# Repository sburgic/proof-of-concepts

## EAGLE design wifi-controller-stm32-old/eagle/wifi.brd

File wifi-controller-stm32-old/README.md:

In order to build project following steps are required:

1. Run cmake configuration script
    1. configure-windows.bat - Windows host, debug version
    2. configure-windows-release.bat - Windows host, release version
    3. configure-linux.sh - Linux host, debug version
    4. configure-linux-release.sh - Linux host, release version
    
2. Go to build-stm32f1-gcc folder ( if it has not already been automatically done from configure script )
   and type make wifi.bin ( or make wifi.bin size - to obtain image size )
   
In order to flash image run load_image_to_flash.sh script from build-stm32f1-gcc folder ( This script can be executed only on Linux )
To flash image using Windows host use STM32 ST-LINK Utility

Tools:
    gcc-arm-none-eabi compiler
    texane st-util for linux
    cmake

Manuals and datasheets in docs folder

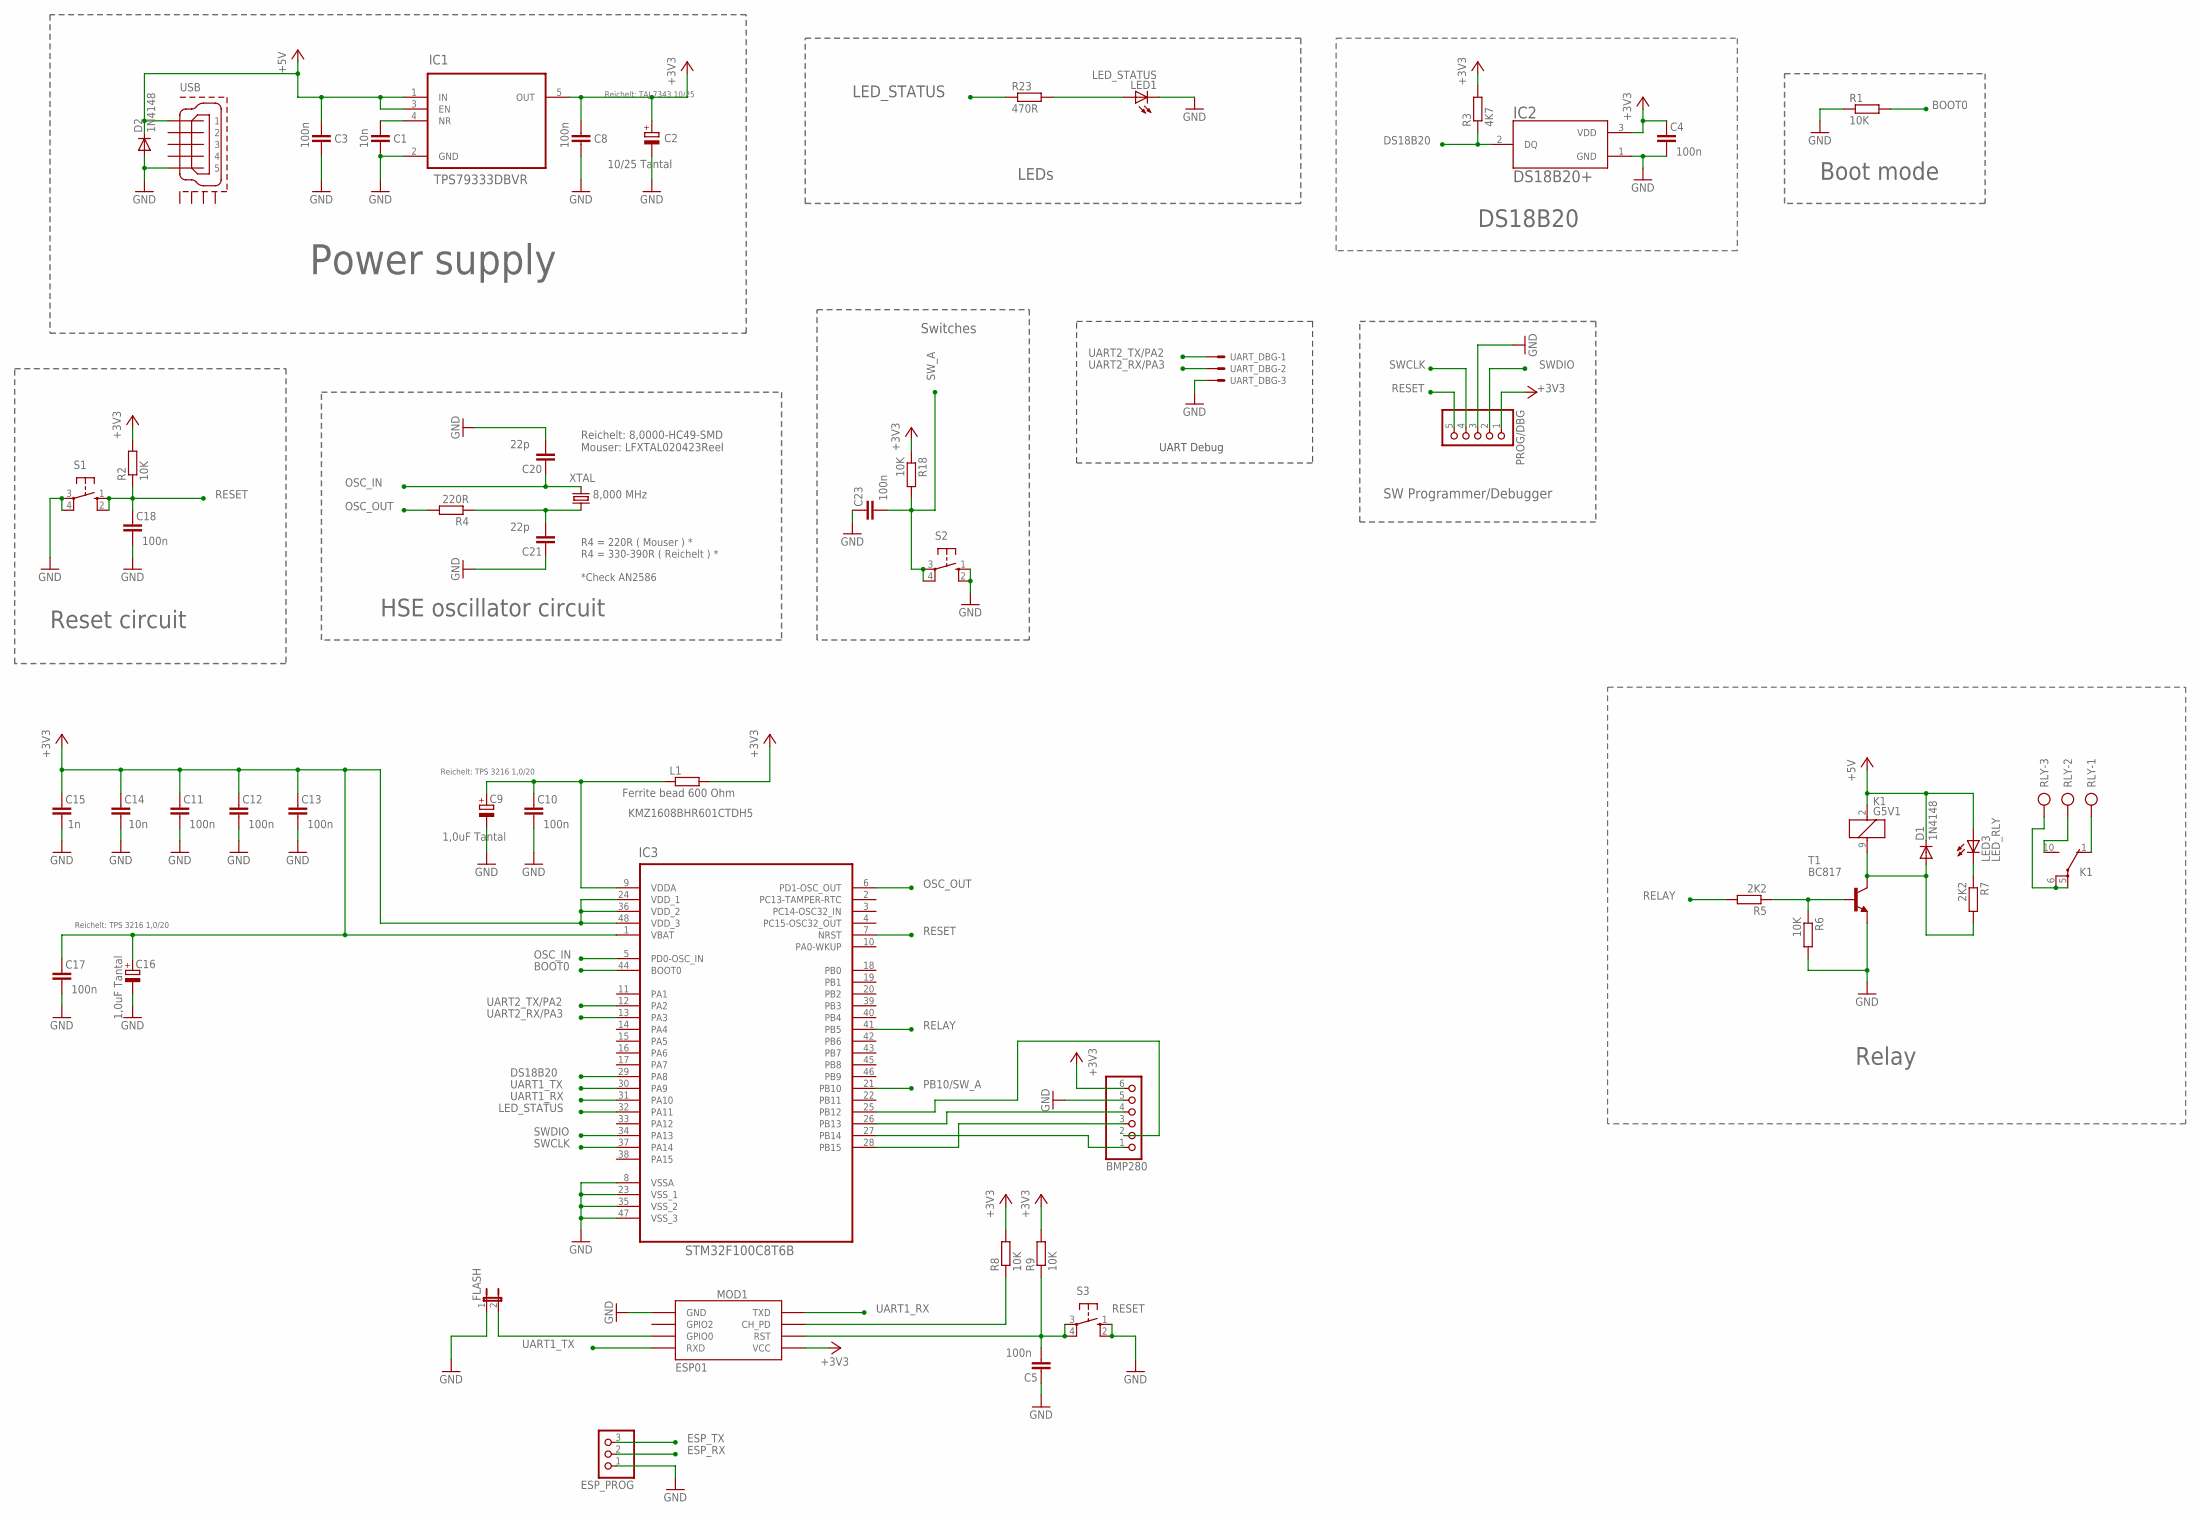
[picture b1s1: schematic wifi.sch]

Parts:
BMP280: PINHD-1X6; 1X06
C1: 10n; C0805
C2: 10/25 Tantal; SMC_D
C3, C4, C5, C8, C23: 100n; C0805
C9, C16: 1,0uF Tantal; SMC_A
C10, C11, C12, C13, C17: 100n; C0402K
C14: 10n; C0402K
C15: 1n; C0402K
C18: 100n; C0603K
C20, C21: 22p; C0603K
D1, D2: 1N4148; DO35-7
ESP_PROG: PINHD-1X3; 1X03
FLASH: JP1E; JP1
IC1: TPS79333DBVR; SOT95P280X145-5N
IC2: DS18B20+; TO-92
IC3: STM32F100C8T6B; QFP50P900X900X160-48N
K1: G5V1
L1: Ferrite bead 600 Ohm; R0603
LED1: LED_STATUS; LED3MM
LED3: LED_RLY; LED3MM
MOD1: ESP01
PROG/DBG: PINHD-1X5; 1X05
R1: 10K; R0805
R2, R6, R8, R9: 10K; R0603
R3: 4K7; R0603
R4: 220R; R0603
R5: 2K2; R0603
R7: 2K2; R0805
R18: 10K; M0805
R23: 470R; R0805
RLY: AK300/3
S1, S2, S3: 10-XX; B3F-10XX
T1: BC817; SOT23-BEC
UART_DBG: 22-23-2031
USB: MICRO-USB-RECEPTACLE47589-0001; 47589-0001
XTAL: 8,000 MHz; SM49

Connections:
+3V3: BMP280.6, C2.+, C4.1, C8.1, C11.1, C12.1, C13.1, C14.1, C15.1, C16.+, C17.1, IC1.5 (OUT), IC2.3 (VDD), IC3.1 (VBAT), IC3.24 (VDD_1), IC3.36 (VDD_2), IC3.48 (VDD_3), L1.2, MOD1.VCC, PROG/DBG.1, R2.2, R3.2, R8.2, R9.2, R18.1
+5V: C3.1, D1.C, D2.C, IC1.1 (IN), IC1.3 (EN), K1.2 (1), LED3.A, USB.1
BOOT0: IC3.44 (BOOT0), R1.2
DS18B20: IC2.2 (DQ), IC3.29 (PA8), R3.1
GND: BMP280.5, C1.2, C2.-, C3.2, C4.2, C5.1, C8.2, C9.-, C10.2, C11.2, C12.2, C13.2, C14.2, C15.2, C16.-, C17.2, C18.2, C20.2, C21.1, C23.1, D2.A, ESP_PROG.1, FLASH.1, IC1.2 (GND), IC2.1 (GND), IC3.8 (VSSA), IC3.23 (VSS_1), IC3.35 (VSS_2), IC3.47 (VSS_3), LED1.K (C), MOD1.GND, PROG/DBG.3, R1.1, R6.2, S1.3, S1.4 (P1), S2.1 (S), S2.2 (S1), S3.1 (S), S3.2 (S1), T1.E, UART_DBG.3, USB.5
LED_STATUS: IC3.32 (PA11), R23.1
unnamed: C1.1, IC1.4 (NR)
unnamed: K1.1 (O), RLY.1
unnamed: C9.+, C10.1, IC3.9 (VDDA), L1.1
unnamed: K1.10 (S), RLY.2
unnamed: K1.5, K1.6, RLY.3
unnamed: C21.2, R4.1, XTAL.2
unnamed: D1.A, K1.9 (2), R7.2, T1.C
unnamed: R5.1, R6.1, T1.B
unnamed: LED3.K (C), R7.1
unnamed: FLASH.2, MOD1.GPIO0
unnamed: MOD1.CH_PD, R8.1
unnamed: C5.2, MOD1.RST, R9.1, S3.3, S3.4 (P1)
unnamed: BMP280.4, IC3.26 (PB13)
unnamed: BMP280.3, IC3.28 (PB15)
unnamed: BMP280.2, IC3.25 (PB12)
unnamed: BMP280.1, IC3.27 (PB14)
unnamed: LED1.A, R23.2
OSC_IN: C20.1, IC3.5 (PD0-OSC_IN), XTAL.1
OSC_OUT: IC3.6 (PD1-OSC_OUT), R4.2
PB10: C23.2, IC3.21 (PB10), R18.2, S2.3, S2.4 (P1)
RELAY: IC3.41 (PB5), R5.2
RESET: C18.1, IC3.7 (NRST), PROG/DBG.5, R2.1, S1.1 (S), S1.2 (S1)
SWCLK: IC3.37 (PA14), PROG/DBG.4
SWDIO: IC3.34 (PA13), PROG/DBG.2
UART1_RX: ESP_PROG.3, IC3.31 (PA10), MOD1.TX (TXD)
UART1_TX: ESP_PROG.2, IC3.30 (PA9), MOD1.RX (RXD)
UART2_RX: IC3.13 (PA3), UART_DBG.2
UART2_TX: IC3.12 (PA2), UART_DBG.1

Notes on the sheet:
KMZ1608BHR601CTDH5
RESET
OSC_OUT
OSC_IN
Reichelt: 8,0000-HC49-SMD Mouser: LFXTAL020423Reel
R4 = 220R ( Mouser ) * R4 = 330-390R ( Reichelt ) * *Check AN2586
BOOT0
UART1_TX
UART1_RX
DS18B20
SWDIO
SWCLK
SW_A
Switches
Power supply
Reset circuit
HSE oscillator circuit
Boot mode
LED_STATUS
LEDs
PB10/SW_A
UART2_TX/PA2
UART2_RX/PA3
Reichelt: TPS 3216 1,0/20
Reichelt: TAJ 7343 10/25
UART Debug
SW Programmer/Debugger
RELAY
Relay
ESP_TX
ESP_RX

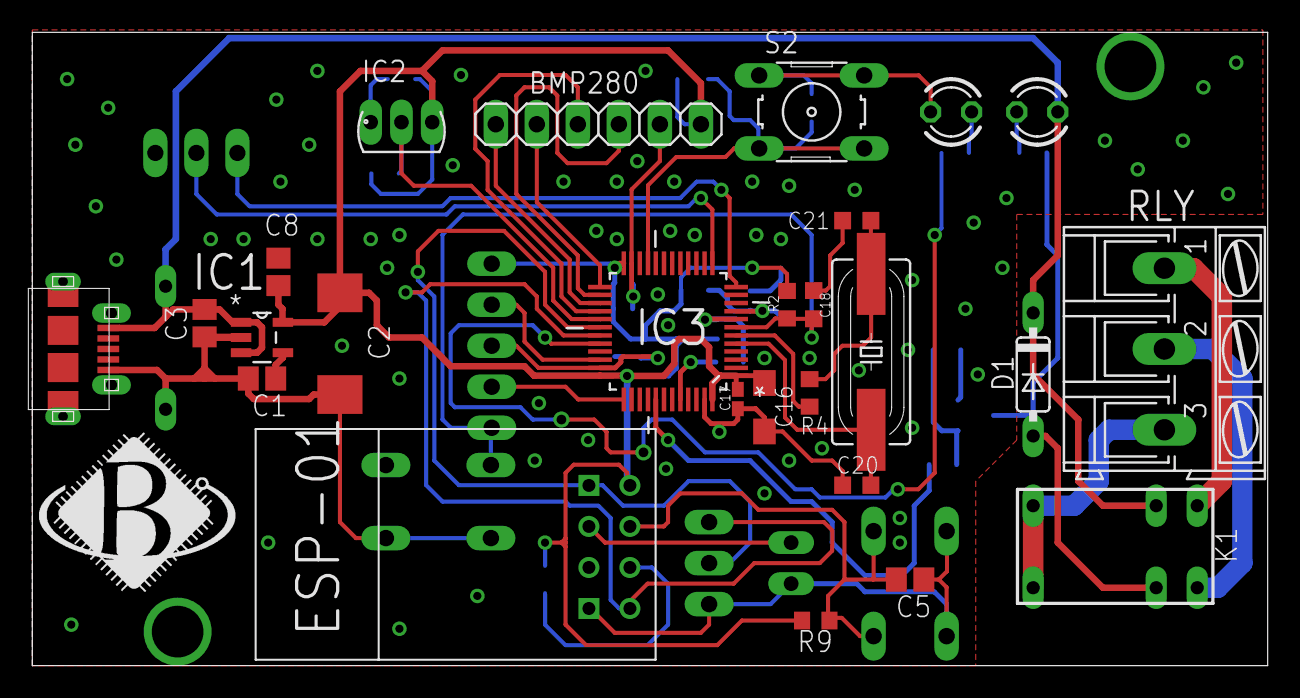
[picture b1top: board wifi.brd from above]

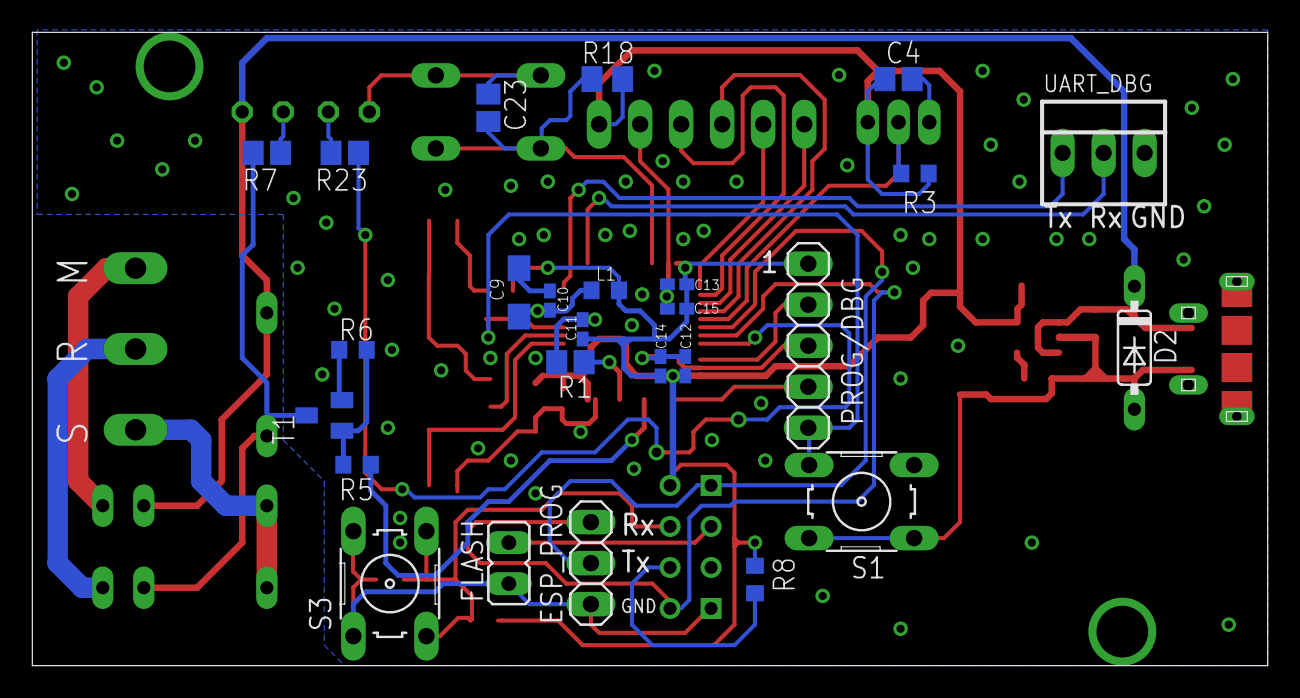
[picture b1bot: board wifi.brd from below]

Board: 2 copper layers, 76.5 x 39.2 mm, 52 parts (26 on the bottom side), 34 nets.

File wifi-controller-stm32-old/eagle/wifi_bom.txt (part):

Partlist exported from D:/!electronics/!projects/wifi/!eagle/wifi.sch at 05/03/2018 22:39:37

Qty Value                Device         Package               Parts                   Description                                                   AVAILABILITY CENTERLINE_(PITCH) COMMENT   DESCRIPTION                                                                                                      MF                   MP             MPN        NUMBER_OF_POSITIONS OC_FARNELL       OC_NEWARK PACKAGE                     PRICE    PRODUCT_TYPE SPICEPREFIX
2                        10-XX          B3F-10XX              S1, S2                  OMRON SWITCH                                                                                                                                                                                                                                                 B3F-1000                       176432           36M3542                                                                
1                        1932788-1      TE_1932788-1          USB                     UUSB 2-DIP REVERSE MOUNT                                      Good         .65 mm[.025 in]    1932788-1  Conn Micro USB RCP 5 POS 0.65mm Solder RA SMD 5 Terminal 1 Port T/R                                             TE                   1932788-1                 5                                              DIP-2 TE Connectivity / AMP 1.46 USD Connector               
1                        22-23-2031     22-23-2031            UART_DBG                .100" (2.54mm) Center Header - 3 Pin                                                                                                                                                                                     MOLEX                               22-23-2031                     1462950          30C0862                                                                
1                        AK300/3        AK300/3               RLY                     CONNECTOR                                                                                                                                                                                                                                                                                   unknown          unknown                                                                
1                        PINHD-1X5      1X05                  PROG/DBG                PIN HEADER                                                                                                                                                                                                                                                                                                                                                                          
2   1,0uF Tantal         CPOL-EUSMCA    SMC_A                 C9, C16                 POLARIZED CAPACITOR, European symbol                                                                                                                                                                                                                                                                                                                                                
1   10/25 Tantal         CPOL-EUSMCD    SMC_D                 C2                      POLARIZED CAPACITOR, European symbol                                                                                                                                                                                                                                                                                                                                                
5   100n                 C-EUC0402K     C0402K                C10, C11, C12, C13, C17 CAPACITOR, European symbol                                                                                                                                                                                                                                                                                                                                               C          
1   100n                 C-EUC0603K     C0603K                C18                     CAPACITOR, European symbol                                                                                                                                                                                                                                                                                                                                               C          
4   100n                 C-EUC0805      C0805                 C3, C4, C8, C23         CAPACITOR, European symbol                                                                                                                                                                                                                                                                                                                                               C          
1   10K                  R-EU_M0805     M0805                 R18                     RESISTOR, European symbol                                                                                                                                                                                                                                                                                                                                                R          
2   10K                  R-EU_R0603     R0603                 R2, R6                  RESISTOR, European symbol                                                                                                                                                                                                                                                                                                                                                R          
1   10K                  R-EU_R0805     R0805                 R1                      RESISTOR, European symbol                                                                                                                                                                                                                                                                                                                                                R          
1   10n                  C-EUC0402K     C0402K                C14                     CAPACITOR, European symbol                                                                                                                                                                                                                                                                                                                                               C          
1   10n                  C-EUC0805      C0805                 C1                      CAPACITOR, European symbol                                                                                                                                                                                                                                                                                                                                               C          
2   1N4148               1N4148DO35-7   DO35-7                D1, D2                  DIODE                                                                                                                                                                                                                                                                                                                                                                               
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
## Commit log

2023-03-21 Add initial projects

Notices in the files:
parts and their libraries:
con-molex-usb: (C) 2014 Tomasz Boleslaw CEDRO, cederom@tlen.pl, http://www.tomek.cedro.info.
